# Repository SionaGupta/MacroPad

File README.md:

# MacroPad
9 Key Macropad with OLED Screen and Rotary Encoder

# CASE

The case has two parts: top and bottom. They are secured through 4 m3 bolts and heat inserts. The bottom of the case has holes for the LED light to shine, as well as a tribute to my favorite movie, How to Train Your Dragon. 

# PCB
This hackpad uses the following schematic and PCB: 

# BOM:
- 9x Cherry MX Switches
- 9x DSA Keycaps
- 4x M3x5x4 Heatset inserts
- 4x M3x16mm SHCS Bolts
- 9x 1N4148 DO-35 Diodes.
- 8x WS2812B LEDs
- 1x 0.91" 128x32 OLED Display
- 1x EC11 Rotary Encoder
- 1x XIAO RP2040
- 1x Case (2 printed parts)

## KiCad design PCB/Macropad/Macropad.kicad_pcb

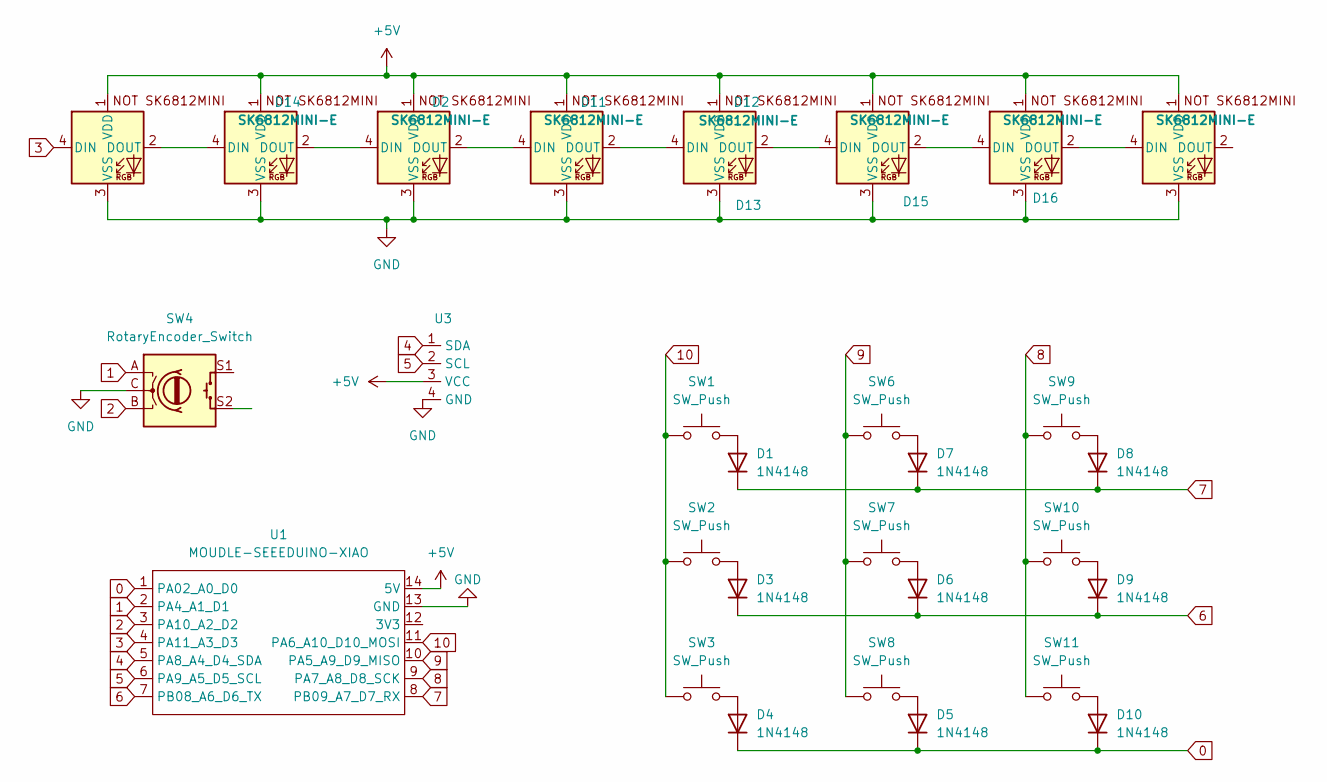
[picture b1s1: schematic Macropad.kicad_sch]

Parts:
D1, D3, D4, D5, D6, D7, D8, D9, D10: 1N4148; D_DO-35_SOD27_P7.62mm_Horizontal
D2, D11, D12, D13, D14, D15, D16, D17: SK6812MINI-E; SK6812MINI-E_fixed
SW1, SW2, SW3, SW6, SW7, SW8, SW9, SW10, SW11: SW_Push; SW_Cherry_MX_1.00u_PCB
SW4: RotaryEncoder_Switch; RotaryEncoder_Alps_EC11E-Switch_Vertical_H20mm
U1: MOUDLE-SEEEDUINO-XIAO; XIAO-Generic-Hybrid-14P-2.54-21X17.8MM
U3: 0.91 OLED Screen

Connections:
0: D4.1 (K), D5.1 (K), D10.1 (K), U1.1 (PA02_A0_D0)
1: SW4.A, U1.2 (PA4_A1_D1)
2: SW4.B, U1.3 (PA10_A2_D2)
3: D14.4 (DIN), U1.4 (PA11_A3_D3)
4: U1.5 (PA8_A4_D4_SDA), U3.1 (SDA)
5: U1.6 (PA9_A5_D5_SCL), U3.2 (SCL)
6: D3.1 (K), D6.1 (K), D9.1 (K), U1.7 (PB08_A6_D6_TX)
7: D1.1 (K), D7.1 (K), D8.1 (K), U1.8 (PB09_A7_D7_RX)
8: SW9.1, SW10.1, SW11.1, U1.9 (PA7_A8_D8_SCK)
9: SW6.1, SW7.1, SW8.1, U1.10 (PA5_A9_D9_MISO)
10: SW1.1, SW2.1, SW3.1, U1.11 (PA6_A10_D10_MOSI)
+5V: D2.1 (VDD), D11.1 (VDD), D12.1 (VDD), D13.1 (VDD), D14.1 (VDD), D15.1 (VDD), D16.1 (VDD), D17.1 (VDD), U1.14 (5V), U3.3 (VCC)
GND: D2.3 (VSS), D11.3 (VSS), D12.3 (VSS), D13.3 (VSS), D14.3 (VSS), D15.3 (VSS), D16.3 (VSS), D17.3 (VSS), SW4.C, U1.13 (GND), U3.4 (GND)
unnamed: D1.2 (A), SW1.2
unnamed: D3.2 (A), SW2.2
unnamed: D4.2 (A), SW3.2
unnamed: D5.2 (A), SW8.2
unnamed: D6.2 (A), SW7.2
unnamed: D7.2 (A), SW6.2
unnamed: D8.2 (A), SW9.2
unnamed: D9.2 (A), SW10.2
unnamed: D10.2 (A), SW11.2
unnamed: D2.2 (DOUT), D11.4 (DIN)
unnamed: D11.2 (DOUT), D12.4 (DIN)
unnamed: D12.2 (DOUT), D13.4 (DIN)
unnamed: D13.2 (DOUT), D15.4 (DIN)
unnamed: D2.4 (DIN), D14.2 (DOUT)
unnamed: D15.2 (DOUT), D16.4 (DIN)
unnamed: D16.2 (DOUT), D17.4 (DIN)

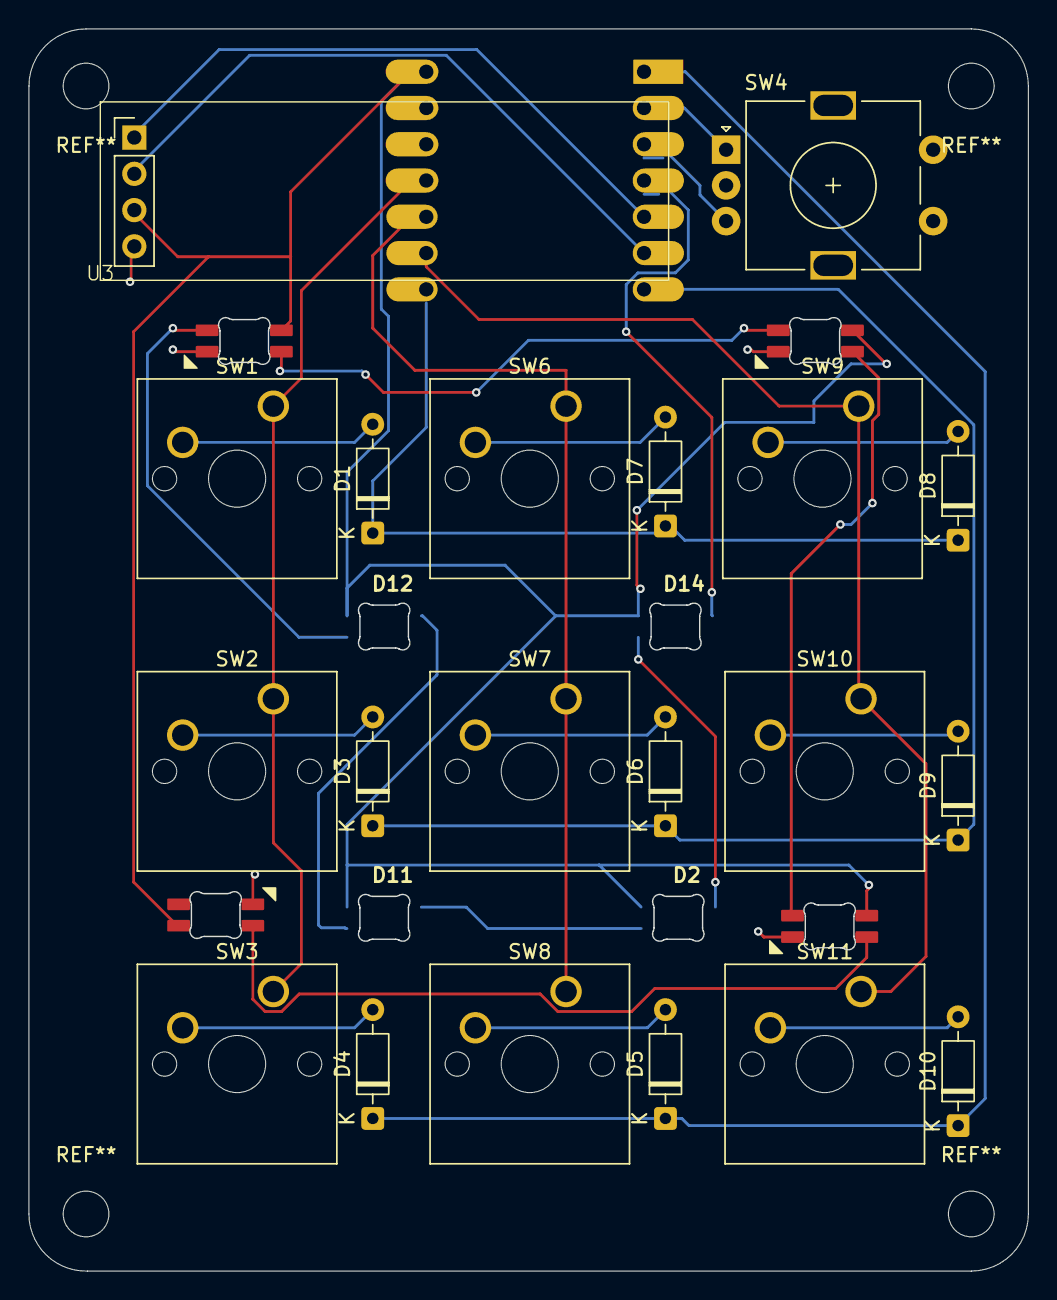
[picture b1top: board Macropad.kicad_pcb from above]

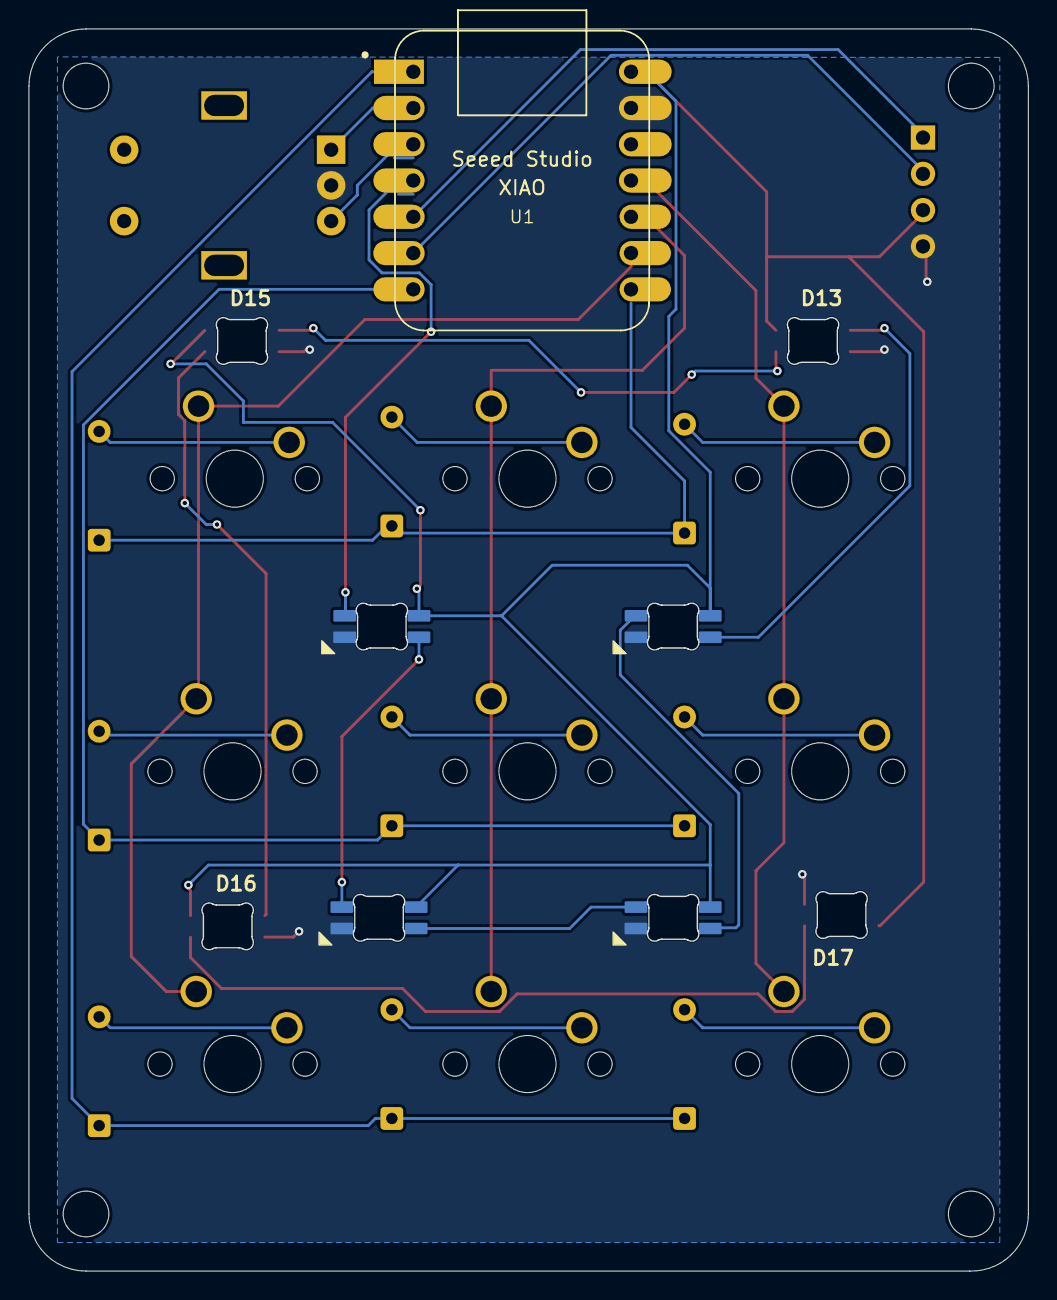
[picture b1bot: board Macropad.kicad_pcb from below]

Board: 2 copper layers, 70.0 x 87.0 mm, 29 parts (5 on the bottom side), 29 nets.

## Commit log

2026-03-30 Add project title and description to README
2026-03-30 Adding Files
2026-03-31 Added Readme
2026-03-31 Add PCB and BOM sections to README
    Updated the README to include PCB and BOM sections with images and details.
2026-03-31 Fix header formatting in README.md
